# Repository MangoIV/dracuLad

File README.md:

# The DracuLad keyboard
This is a 34-36-key-board.
## Features
- 36 keys, two of them can be replaced by rotary encoders making it support 34-36 keys and 2-4 encoders. 
- bright RGB Underglow with WS2812b LEDs
- one SSD1306 OLED per side
- support for the [pimoroni trackball](https://shop.pimoroni.com/products/trackball-breakout)
- powered by QMK-firmware (Firmware has been merged and can be found on [the QMK master](https://github.com/qmk/qmk_firmware/))
- aggressive pinky stagger similar to the Kyria but with a slightly alternative thumb cluster to raise comfort for large hands
- support for MX and Kailh choc v1 switches
- files for fr4 plate and acrylic bottom plate as well as OLED window

## State of the project
- PCBs are fully working (OLED, LEDs, all switches, encoders, Trackball)
- acrylic plates have arrived and fit perfectly
- 3D-printable case has been added thanks to the awesome work of Sadek Baroudi
- basic ZMK Firmware (not all features implemented yet) exists on [my fork of the zmk firmware](https://github.com/MangoIV/zmk.git)

## Hardware availability
- hardware availability is always a big problem and ordering everything yourself is a big hustle. Therefore I'm happy to tell you that Ben from keycapsss (not me) is so kind [to offer everything to make a full build](https://keycapsss.com/). And for those of you who are American, [littlekeyboards](https://www.littlekeyboards.com/) (also not me) also offers kits
- if you live in a remote area resulting in high shipping costs or problems with importing, gerbers for ordering the PCBs and SVGs for getting plates cut are available in this repo, too

## Things to consider before getting a DracuLad
- for the upper encoder you can't use the really big guitar knobs as they're too wide and will interfere with the OLEDs, the smaller ones are recommended
- the thumb cluster is lower than on boards like the Corne keyboard
- liking or disliking a layout is not a matter of how "good" the layout is but mostly preference, hence I recommend looking at [a split keyboard comparison site](https://jhelvy.shinyapps.io/splitkbcompare/) and print out some layouts to confirm you like it. (DracuLad can be found there, too)
- before purchasing encoders, make sure they fit! The holes in the plate are 12mm x 12mm and won't fit bigger encoders. They're in particular not the size of the switch footprints.

## Some pictures to get your mouth watery

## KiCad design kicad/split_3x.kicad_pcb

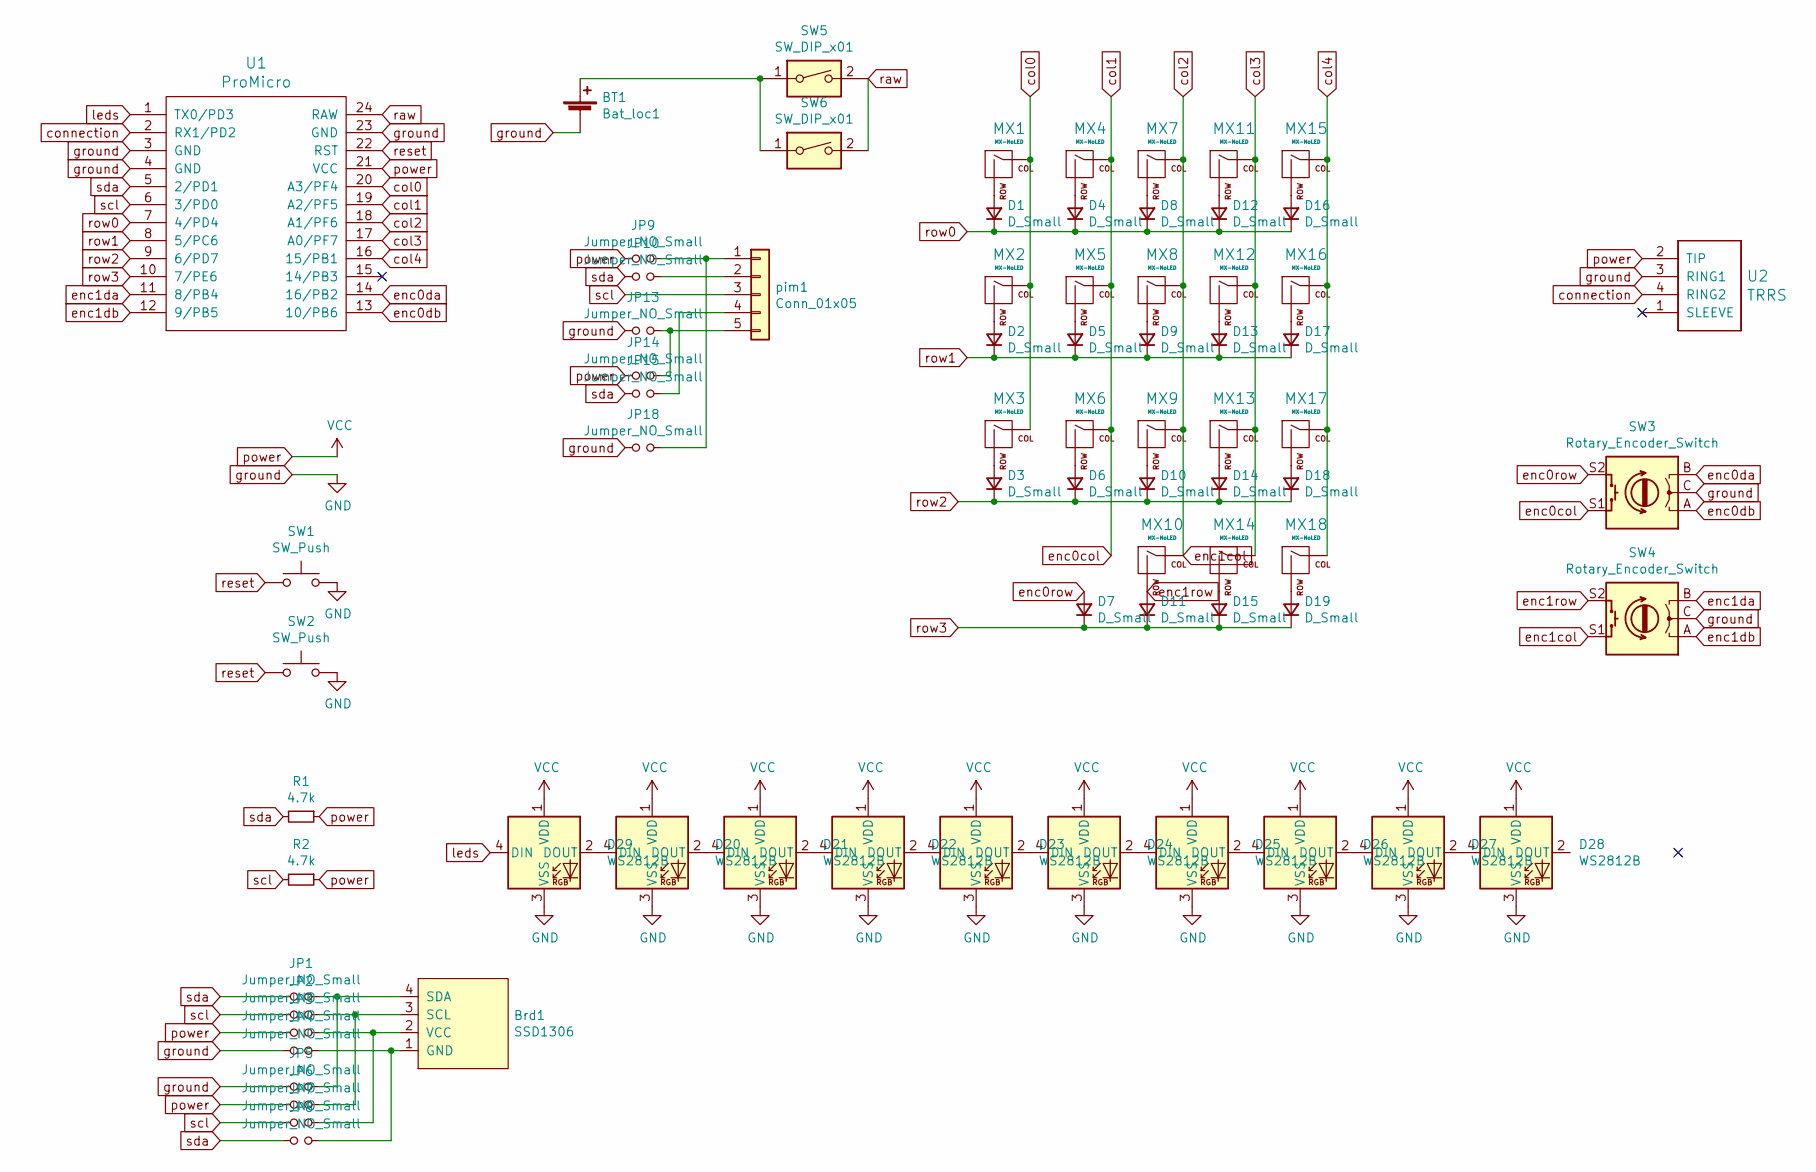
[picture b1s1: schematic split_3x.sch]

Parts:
BT1: Bat_loc1; PinHeader_1x02_P2.00mm_Vertical
Brd1: SSD1306; 128x64OLED
D1, D2, D3, D4, D5, D6, D7, D8, D9, D10, D11, D12, D13, D14, D15, D16, D17, D18, D19: D_Small; D_SOD123F
D20, D21, D22, D23, D24, D25, D26, D27, D28, D29: WS2812B
JP1, JP2, JP3, JP4, JP5, JP6, JP7, JP8, JP9, JP10, JP13, JP14, JP15, JP18: Jumper_NO_Small; SolderJumper-2_P1.3mm_Open_RoundedPad1.0x1.5mm
MX1, MX2, MX3, MX4, MX5, MX6, MX7, MX8, MX9, MX10, MX11, MX12, MX13, MX14, MX15, MX16, MX17, MX18: MX-NoLED; CherryMX_Choc_1u_reversible
R1, R2: 4.7k; R_0805_2012Metric
SW1, SW2: SW_Push; SW_SPST_TL3342
SW3, SW4: Rotary_Encoder_Switch; RotaryEncoder_EC11-no-legs
SW5, SW6: SW_DIP_x01; switch_MSK-12C02_smd
U1: ProMicro
U2: TRRS; TRRS-PJ-320A-dual
pim1: Conn_01x05; pimoroni_left_side_mount

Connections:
unnamed: BT1.1 (+), SW5.1, SW6.1
unnamed: Brd1.1 (GND), JP4.2, JP8.2
unnamed: Brd1.2 (VCC), JP3.2, JP7.2
unnamed: Brd1.3 (SCL), JP2.2, JP6.2
unnamed: Brd1.4 (SDA), JP1.2, JP5.2
unnamed: D1.2 (A), MX1.2 (ROW)
unnamed: D2.2 (A), MX2.2 (ROW)
unnamed: D3.2 (A), MX3.2 (ROW)
unnamed: D4.2 (A), MX4.2 (ROW)
unnamed: D5.2 (A), MX5.2 (ROW)
unnamed: D6.2 (A), MX6.2 (ROW)
unnamed: D8.2 (A), MX7.2 (ROW)
unnamed: D9.2 (A), MX8.2 (ROW)
unnamed: D10.2 (A), MX9.2 (ROW)
unnamed: D12.2 (A), MX11.2 (ROW)
unnamed: D13.2 (A), MX12.2 (ROW)
unnamed: D14.2 (A), MX13.2 (ROW)
unnamed: D15.2 (A), MX14.2 (ROW)
unnamed: D16.2 (A), MX15.2 (ROW)
unnamed: D17.2 (A), MX16.2 (ROW)
unnamed: D18.2 (A), MX17.2 (ROW)
unnamed: D19.2 (A), MX18.2 (ROW)
unnamed: D20.2 (DOUT), D21.4 (DIN)
unnamed: D20.4 (DIN), D29.2 (DOUT)
unnamed: D21.2 (DOUT), D22.4 (DIN)
unnamed: D22.2 (DOUT), D23.4 (DIN)
unnamed: D23.2 (DOUT), D24.4 (DIN)
unnamed: D24.2 (DOUT), D25.4 (DIN)
unnamed: D25.2 (DOUT), D26.4 (DIN)
unnamed: D26.2 (DOUT), D27.4 (DIN)
unnamed: D27.2 (DOUT), D28.4 (DIN)
unnamed: JP10.2, pim1.2
unnamed: JP13.2, JP14.2, pim1.5
unnamed: JP15.2, pim1.4
unnamed: JP9.2, JP18.2, pim1.1
col0: MX1.1 (COL), MX2.1 (COL), MX3.1 (COL), U1.20 (A3/PF4)
col1: MX4.1 (COL), MX5.1 (COL), MX6.1 (COL), SW3.S1, U1.19 (A2/PF5)
col2: MX7.1 (COL), MX8.1 (COL), MX9.1 (COL), MX10.1 (COL), SW4.S1, U1.18 (A1/PF6)
col3: MX11.1 (COL), MX12.1 (COL), MX13.1 (COL), MX14.1 (COL), U1.17 (A0/PF7)
col4: MX15.1 (COL), MX16.1 (COL), MX17.1 (COL), MX18.1 (COL), U1.16 (15/PB1)
connection: U1.2 (RX1/PD2), U2.4 (RING2)
enc0da: SW3.B, U1.14 (16/PB2)
enc0db: SW3.A, U1.13 (10/PB6)
enc0row: D7.2 (A), SW3.S2
enc1da: SW4.B, U1.11 (8/PB4)
enc1db: SW4.A, U1.12 (9/PB5)
enc1row: D11.2 (A), MX10.2 (ROW), SW4.S2
ground: BT1.2 (-), D20.3 (VSS), D21.3 (VSS), D22.3 (VSS), D23.3 (VSS), D24.3 (VSS), D25.3 (VSS), D26.3 (VSS), D27.3 (VSS), D28.3 (VSS), D29.3 (VSS), JP4.1, JP5.1, JP13.1, JP18.1, SW1.2, SW2.2, SW3.C, SW4.C, U1.3 (GND), U1.4 (GND), U1.23 (GND), U2.3 (RING1)
leds: D29.4 (DIN), U1.1 (TX0/PD3)
power: D20.1 (VDD), D21.1 (VDD), D22.1 (VDD), D23.1 (VDD), D24.1 (VDD), D25.1 (VDD), D26.1 (VDD), D27.1 (VDD), D28.1 (VDD), D29.1 (VDD), JP3.1, JP6.1, JP9.1, JP14.1, R1.1, R2.1, U1.21 (VCC), U2.2 (TIP)
raw: SW5.2, SW6.2, U1.24 (RAW)
reset: SW1.1, SW2.1, U1.22 (RST)
row0: D1.1 (K), D4.1 (K), D8.1 (K), D12.1 (K), D16.1 (K), U1.7 (4/PD4)
row1: D2.1 (K), D5.1 (K), D9.1 (K), D13.1 (K), D17.1 (K), U1.8 (5/PC6)
row2: D3.1 (K), D6.1 (K), D10.1 (K), D14.1 (K), D18.1 (K), U1.9 (6/PD7)
row3: D7.1 (K), D11.1 (K), D15.1 (K), D19.1 (K), U1.10 (7/PE6)
scl: JP2.1, JP7.1, R2.2, U1.6 (3/PD0), pim1.3
sda: JP1.1, JP8.1, JP10.1, JP15.1, R1.2, U1.5 (2/PD1)

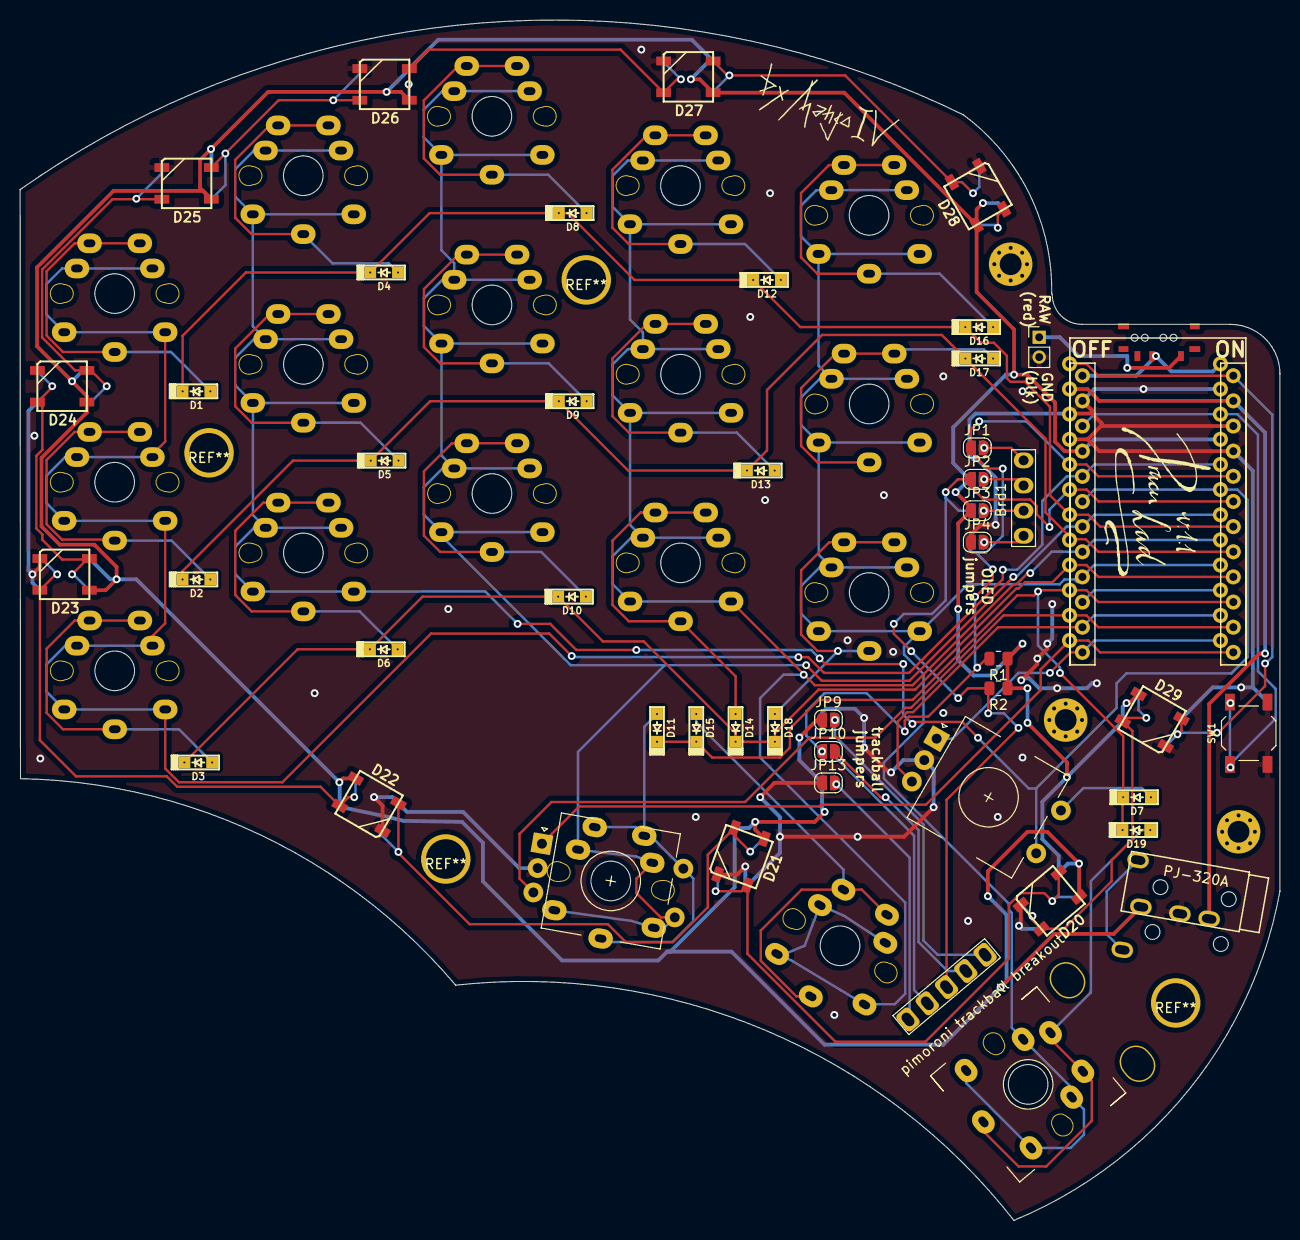
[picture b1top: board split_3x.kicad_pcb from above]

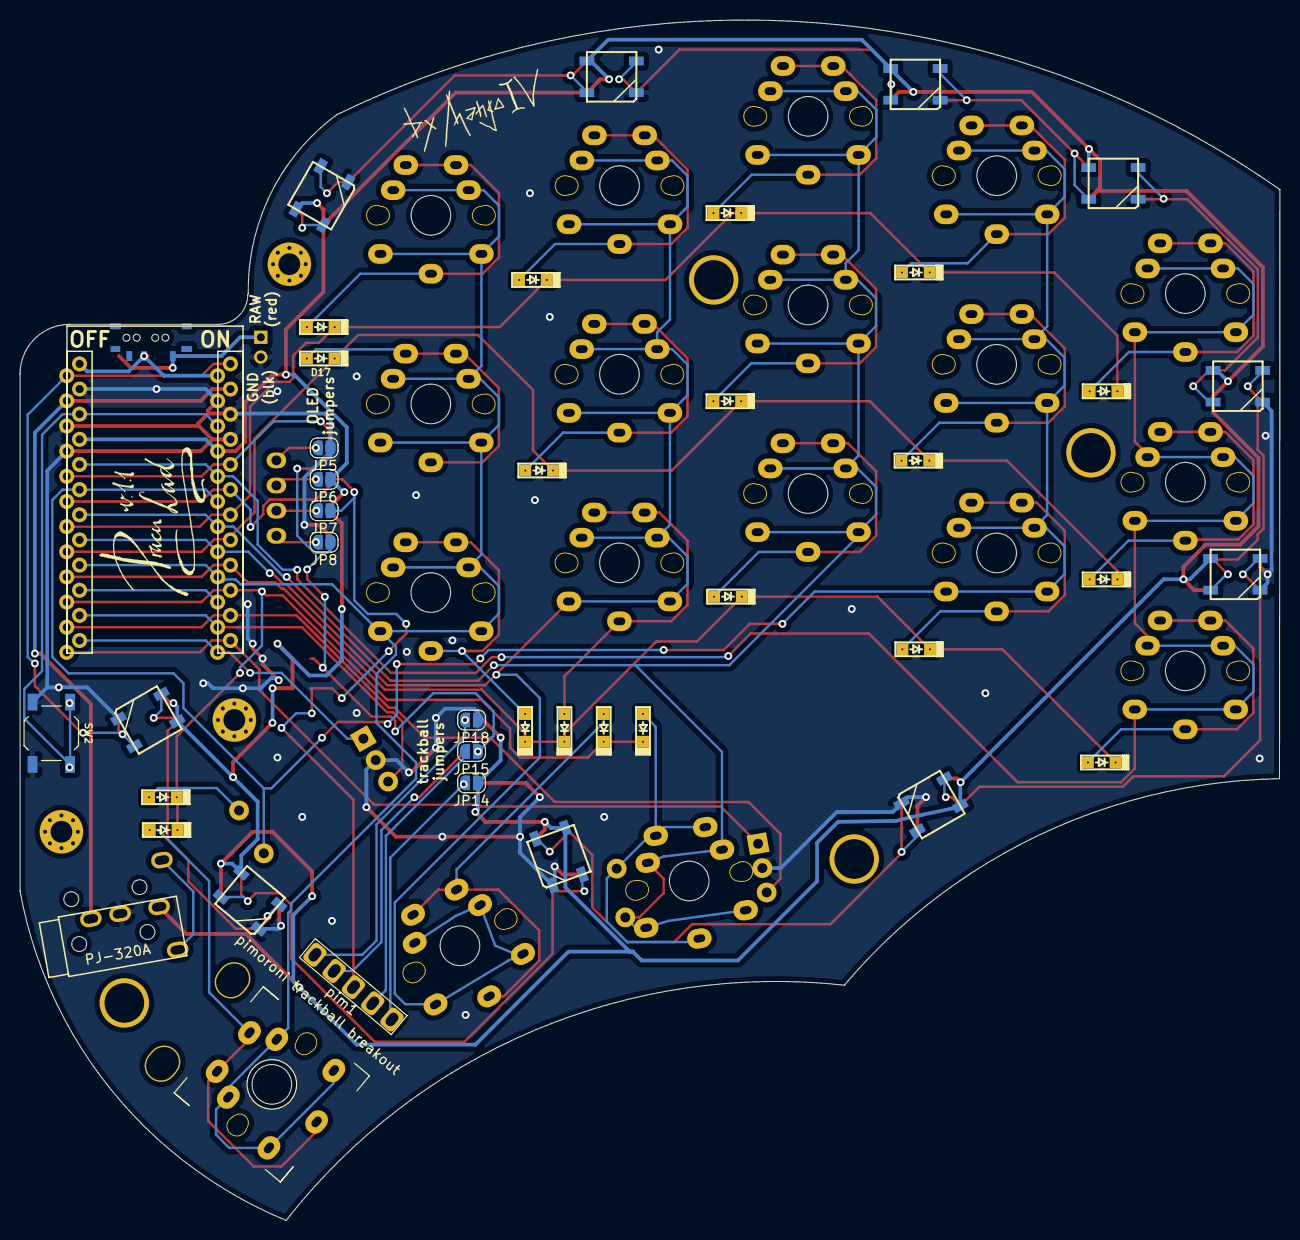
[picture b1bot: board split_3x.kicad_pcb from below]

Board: 2 copper layers, 127.3 x 121.2 mm, 77 parts (10 on the bottom side), 58 nets.

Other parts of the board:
 : MountingHole_2.2mm_M2_Pad_Via
 #2,  #3: MountingHole_2.2mm_M2_Pad_Via

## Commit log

2020-11-15 created project
2020-11-15 added some other components footpritns
2020-11-15 added part of the schematic
2020-11-16 started the pcb
2020-11-16 finished putting the parts in order, time to route
2020-11-16 replaced some things, added edgecuts
2020-11-16 added some routing
2020-11-16 finished routing
2020-11-16 added art and text
2020-11-16 added gerbers
2020-11-17 added plate
2020-11-17 added plate and gerbers
2020-11-24 added svg for bottom plate
2020-11-30 added pictures
2020-12-06 added some pictures
2020-12-07 changed the plate to have copper pane, updated gerbers of pcb and plate
2021-01-03 added pic of low pro build
2021-01-05 added support for the pimoroni trackball breakout, changed a bunch of things, rewired the pcb, changed the bottom plate to be prettier, added some silkscreen, changed the position of one of the mount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
2021-01-06 generated gerbers for the second run
2021-01-18 dunno when i last pushed therefore I'm commiting
2021-01-19 added svg for acrylic plate cutting
2021-03-01 added pictures of rev2
2021-04-16 Case 3d model with stls, and pictures of the build
2021-04-16 Added some awesome features and changed the README accordingly.
2021-04-16 Typo in my name, whoops
2021-04-27 PR to qmk got merged, updated README accordingly
2021-08-05 adde a footprint to solder a battery and smd switches to toggle it
2021-08-05 modified the silkscreen to work better with the battery
    :
2021-08-05 zipped gerbers
2021-08-05 added plate that is better for large encoder bases
2021-08-08 added v1.1 silkscreenart, added mangoiv logo, moved the switch footprint a little bit
2024-03-07 [fix] remove outdated information in README
